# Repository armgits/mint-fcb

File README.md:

# Mint

Mint Flight Controller Board is compact under a 27 mm square to fit on Micro/Nano class drones using a standard 20 x 20 mm mount. Despite the small form factor, it features a comprehensive set of IO interfaces for a wide range of peripherals.

This repository hosts the KiCAD project of the flight controller board.

> - The PCB design is still under completion. This board has never been built and tested.
> - Firmware for this target does not exist yet.

## Specifications

- **Processor and Sensors**
  - STM32H723VIH6 MCU
  - ICM20602 and BMI088 IMUs
  - DPS310 Barometer

- **Interfaces**
  - 10x PWM outputs (8 for motors and 2 for peripherals)
  - 1x RC input (UART 1)
  - 1x I2C bus for external sensors
  - 1x CAN bus for external sensors
  - 5x UARTs
  - 4-in-1 ESC interface for Motor outputs 1-4
  - DJI Air Unit interface (UART 8)
  - 3x GPIO pins
  - 1x microSD card slot for logging

- **Power**
  - 4V - 32V voltage input (2S-7S)
  - Onboard 5V, 2A BEC for low-power peripherals

- **Physical Dimensions**
  - 26.5 x 26.25 mm
  - 20 x 20 mm, M2 mount pattern

## Images

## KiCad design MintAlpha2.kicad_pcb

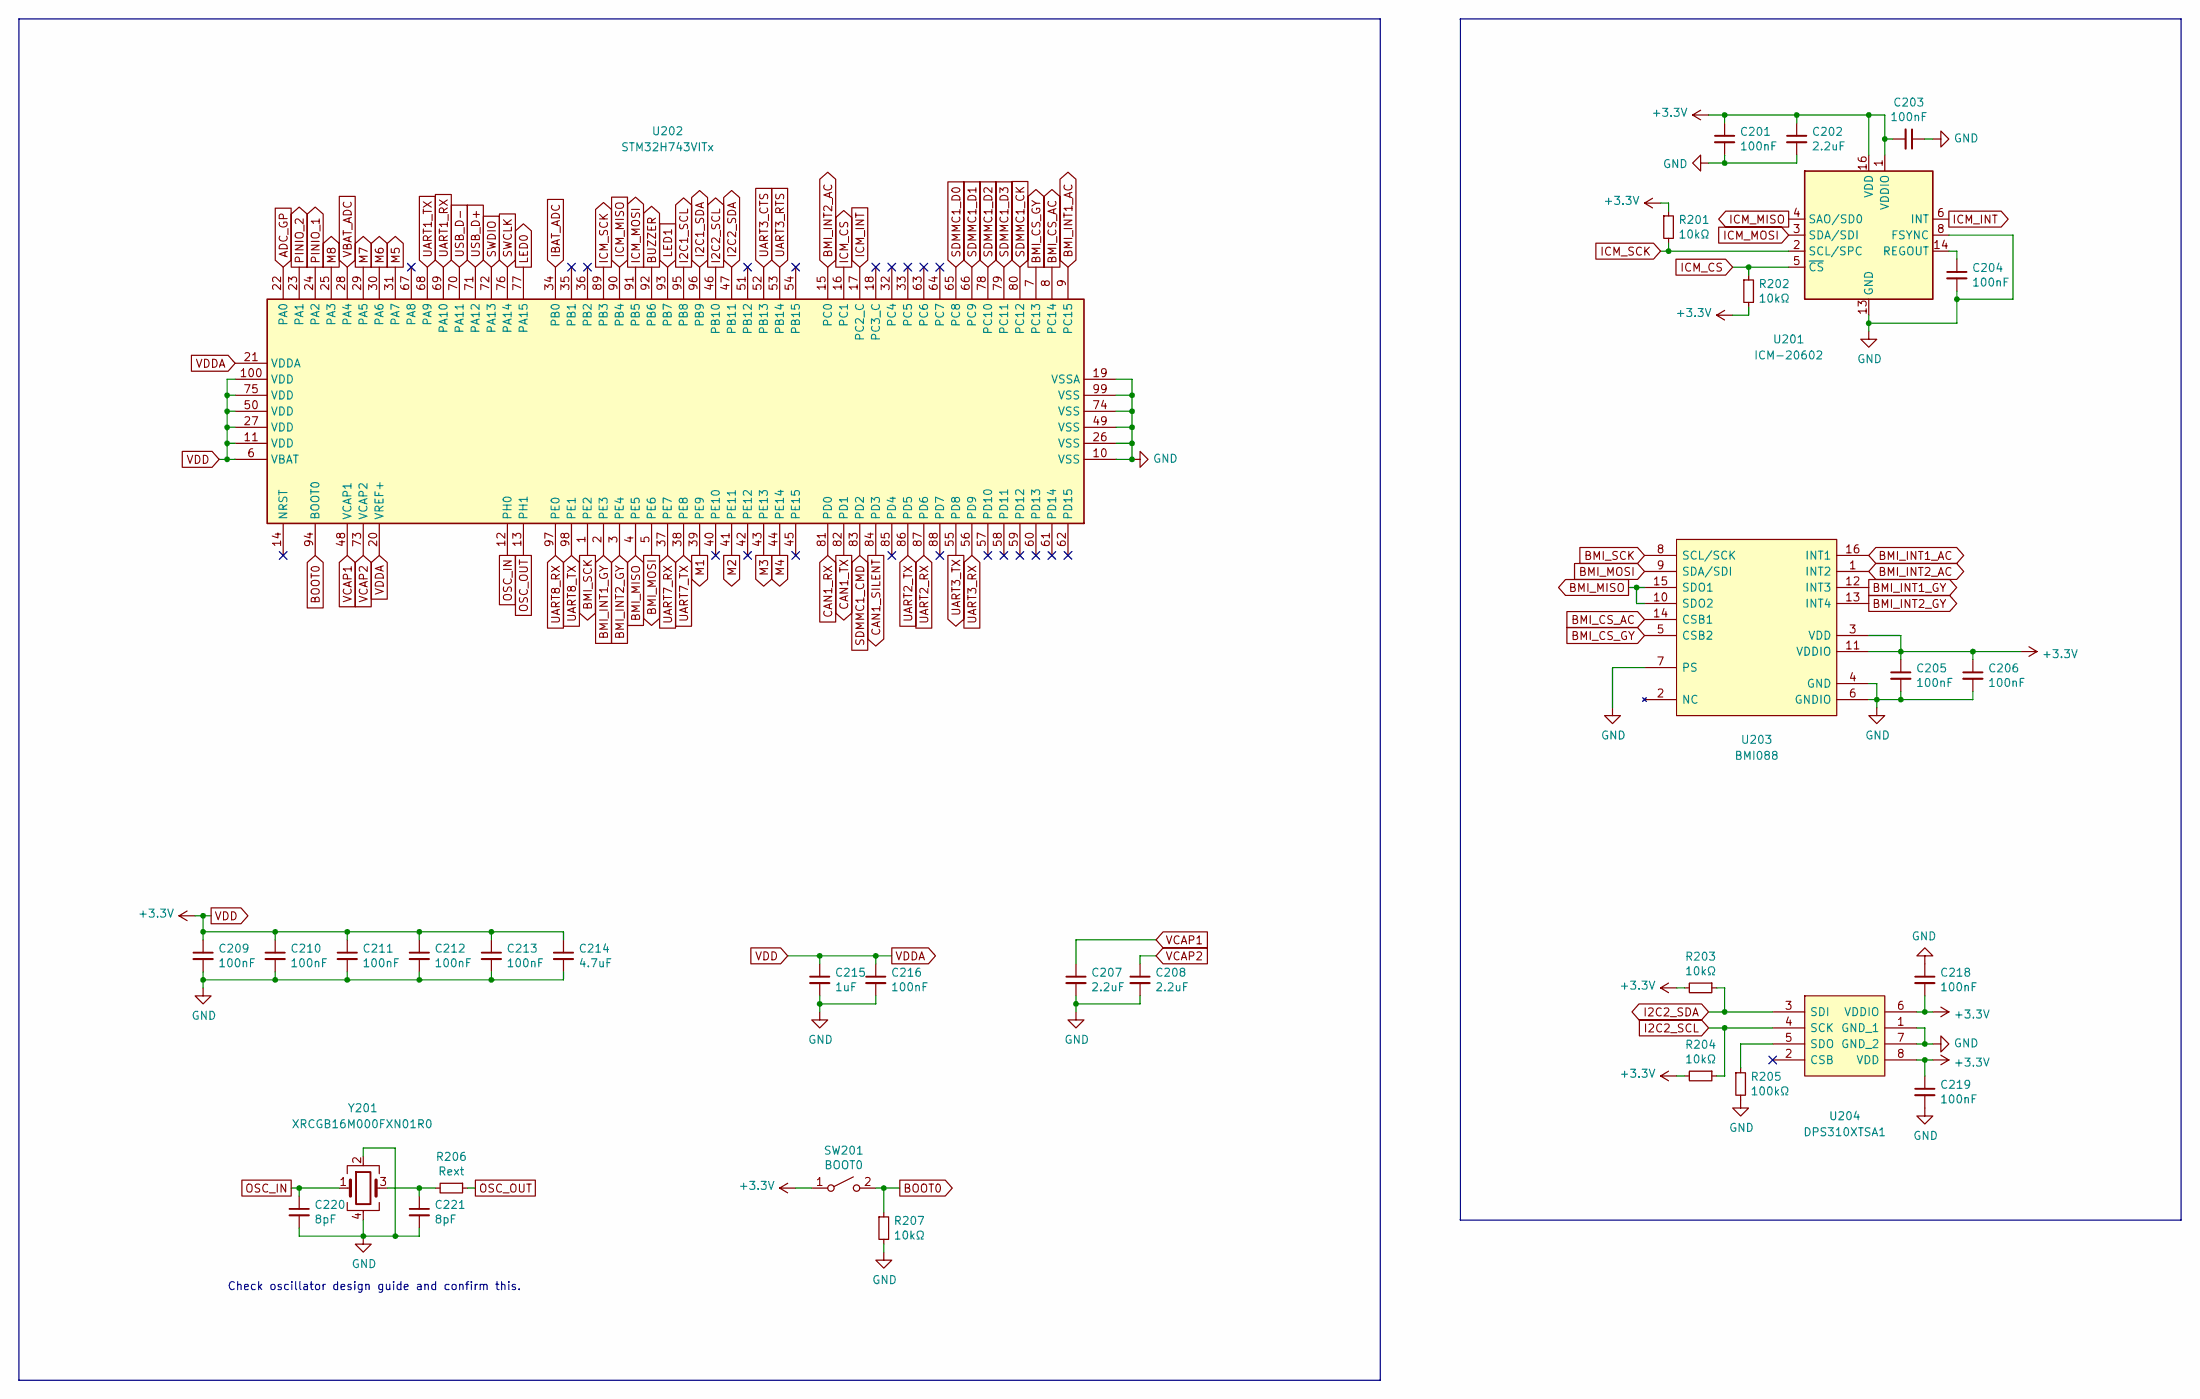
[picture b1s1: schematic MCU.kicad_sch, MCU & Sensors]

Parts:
C201, C203, C204, C205, C206, C209, C210, C211, C212, C213, C216, C218, C219: 100nF; C_0402_1005Metric; Part No. C0402C104K4RAC7411
C202, C207, C208: 2.2uF; C_0402_1005Metric; Part No. LMK105BJ225KV-F
C214: 4.7uF; C_0603_1608Metric; Part No. LMK107BJ475MAHT
C215: 1uF; C_0402_1005Metric; Part No. LMK105BJ105MVHF
C220, C221: 8pF; C_0402_1005Metric; Part No. GJM1555C1H8R0CB01D
R201, R202, R203, R204, R207: 10kΩ; R_0402_1005Metric; Part No. RC0402FR-0710KL
R205: 100kΩ; R_0402_1005Metric; Part No. RC0402FR-07100KL
R206: Rext; R_0402_1005Metric
SW201: BOOT0; TactileSwitch_B3U-1000P_SPST_NO; Part No. KMS233GLFG
U201: ICM-20602; LGA-16_3x3mm_P0.5mm_LayoutBorder3x5y; Part No. ICM-20602
U202: STM32H743VITx; LQFP-100_14x14mm_P0.5mm
U203: BMI088; BMI088_LGA16_4.5x3mm_P0.5mm; Part No. BMI088
U204: DPS310XTSA1; DPS310_PG-VLGA-8-1; Part No. DPS310XTSA1
Y201: XRCGB16M000FXN01R0; Crystal_Murata_XRCGB_F_P_HCR2016; Part No. XRCGB16M000FXN01R0

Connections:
ADC_GP: U202.22 (PA0); also elsewhere on the board
BMI_CS_AC: U202.8 (PC14), U203.14 (CSB1)
BMI_CS_GY: U202.7 (PC13), U203.5 (CSB2)
BMI_INT1_AC: U202.9 (PC15), U203.16 (INT1)
BMI_INT1_GY: U202.2 (PE3), U203.12 (INT3)
BMI_INT2_AC: U202.15 (PC0), U203.1 (INT2)
BMI_INT2_GY: U202.3 (PE4), U203.13 (INT4)
BMI_MISO: U202.4 (PE5), U203.10 (SDO2), U203.15 (SDO1)
BMI_MOSI: U202.5 (PE6), U203.9 (SDA/SDI)
BMI_SCK: U202.1 (PE2), U203.8 (SCL/SCK)
BOOT0: R207.1, SW201.2 (B), U202.94 (BOOT0)
BUZZER: U202.92 (PB6); also elsewhere on the board
CAN1_RX: U202.81 (PD0); also elsewhere on the board
CAN1_SILENT: U202.84 (PD3); also elsewhere on the board
CAN1_TX: U202.82 (PD1); also elsewhere on the board
GND: C201.2, C202.2, C203.1, C204.2, C205.2, C206.2, C207.2, C208.2, C209.2, C210.2, C211.2, C212.2, C213.2, C214.2, C215.2, C216.2, C218.1, C219.2, C220.2, C221.2, R205.2, R207.2, U201.8 (FSYNC), U201.9 (GND), U201.10 (GND), U201.11 (GND), U201.12 (GND), U201.13 (GND), U201.15 (GND), U202.10 (VSS), U202.19 (VSSA), U202.26 (VSS), U202.49 (VSS), U202.74 (VSS), U202.99 (VSS), U203.4 (GND), U203.6 (GNDIO), U203.7 (PS), U204.1 (GND_1), U204.7 (GND_2), Y201.2, Y201.4; also elsewhere on the board
I2C1_SCL: U202.95 (PB8); also elsewhere on the board
I2C1_SDA: U202.96 (PB9); also elsewhere on the board
I2C2_SCL: R204.1, U202.46 (PB10), U204.4 (SCK)
I2C2_SDA: R203.1, U202.47 (PB11), U204.3 (SDI)
IBAT_ADC: U202.34 (PB0); also elsewhere on the board
ICM_CS: R202.1, U201.5 (~CS), U202.16 (PC1)
ICM_INT: U201.6 (INT), U202.17 (PC2_C)
ICM_MISO: U201.4 (SAO/SD0), U202.90 (PB4)
ICM_MOSI: U201.3 (SDA/SDI), U202.91 (PB5)
ICM_SCK: R201.2, U201.2 (SCL/SPC), U202.89 (PB3)
LED0: U202.77 (PA15); also elsewhere on the board
LED1: U202.93 (PB7); also elsewhere on the board
M1: U202.39 (PE9); also elsewhere on the board
M2: U202.41 (PE11); also elsewhere on the board
M3: U202.43 (PE13); also elsewhere on the board
M4: U202.44 (PE14); also elsewhere on the board
M5: U202.31 (PA7); also elsewhere on the board
M6: U202.30 (PA6); also elsewhere on the board
M7: U202.29 (PA5); also elsewhere on the board
M8: U202.25 (PA3); also elsewhere on the board
unnamed: C204.1, U201.14 (REGOUT)
unnamed: C221.1, R206.2, Y201.3
unnamed: R205.1, U204.5 (SDO)
OSC_IN: C220.1, U202.12 (PH0), Y201.1
OSC_OUT: R206.1, U202.13 (PH1)
PINIO_1: U202.24 (PA2); also elsewhere on the board
PINIO_2: U202.23 (PA1); also elsewhere on the board
SDMMC1_CK: U202.80 (PC12); also elsewhere on the board
SDMMC1_CMD: U202.83 (PD2); also elsewhere on the board
SDMMC1_D0: U202.65 (PC8); also elsewhere on the board
SDMMC1_D1: U202.66 (PC9); also elsewhere on the board
SDMMC1_D2: U202.78 (PC10); also elsewhere on the board
SDMMC1_D3: U202.79 (PC11); also elsewhere on the board
SWCLK: U202.76 (PA14); also elsewhere on the board
SWDIO: U202.72 (PA13); also elsewhere on the board
UART1_RX: U202.69 (PA10); also elsewhere on the board
UART1_TX: U202.68 (PA9); also elsewhere on the board
UART2_RX: U202.87 (PD6); also elsewhere on the board
UART2_TX: U202.86 (PD5); also elsewhere on the board
UART3_CTS: U202.52 (PB13); also elsewhere on the board
UART3_RTS: U202.53 (PB14); also elsewhere on the board
UART3_RX: U202.56 (PD9); also elsewhere on the board
UART3_TX: U202.55 (PD8); also elsewhere on the board
UART7_RX: U202.37 (PE7); also elsewhere on the board
UART7_TX: U202.38 (PE8); also elsewhere on the board
UART8_RX: U202.97 (PE0); also elsewhere on the board
UART8_TX: U202.98 (PE1); also elsewhere on the board
USB_D+: U202.71 (PA12); also elsewhere on the board
USB_D-: U202.70 (PA11); also elsewhere on the board
VBAT_ADC: U202.28 (PA4); also elsewhere on the board
VCAP1: C207.1, U202.48 (VCAP1)
VCAP2: C208.1, U202.73 (VCAP2)
VDD: C201.1, C202.1, C203.2, C205.1, C206.1, C209.1, C210.1, C211.1, C212.1, C213.1, C214.1, C215.1, C216.1, C218.2, C219.1, R201.1, R202.2, R203.2, R204.2, SW201.1 (A), U201.1 (VDDIO), U201.16 (VDD), U202.6 (VBAT), U202.11 (VDD), U202.20 (VREF+), U202.21 (VDDA), U202.27 (VDD), U202.50 (VDD), U202.75 (VDD), U202.100 (VDD), U203.3 (VDD), U203.11 (VDDIO), U204.6 (VDDIO), U204.8 (VDD); also elsewhere on the board

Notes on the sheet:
Check oscillator design guide and confirm this.

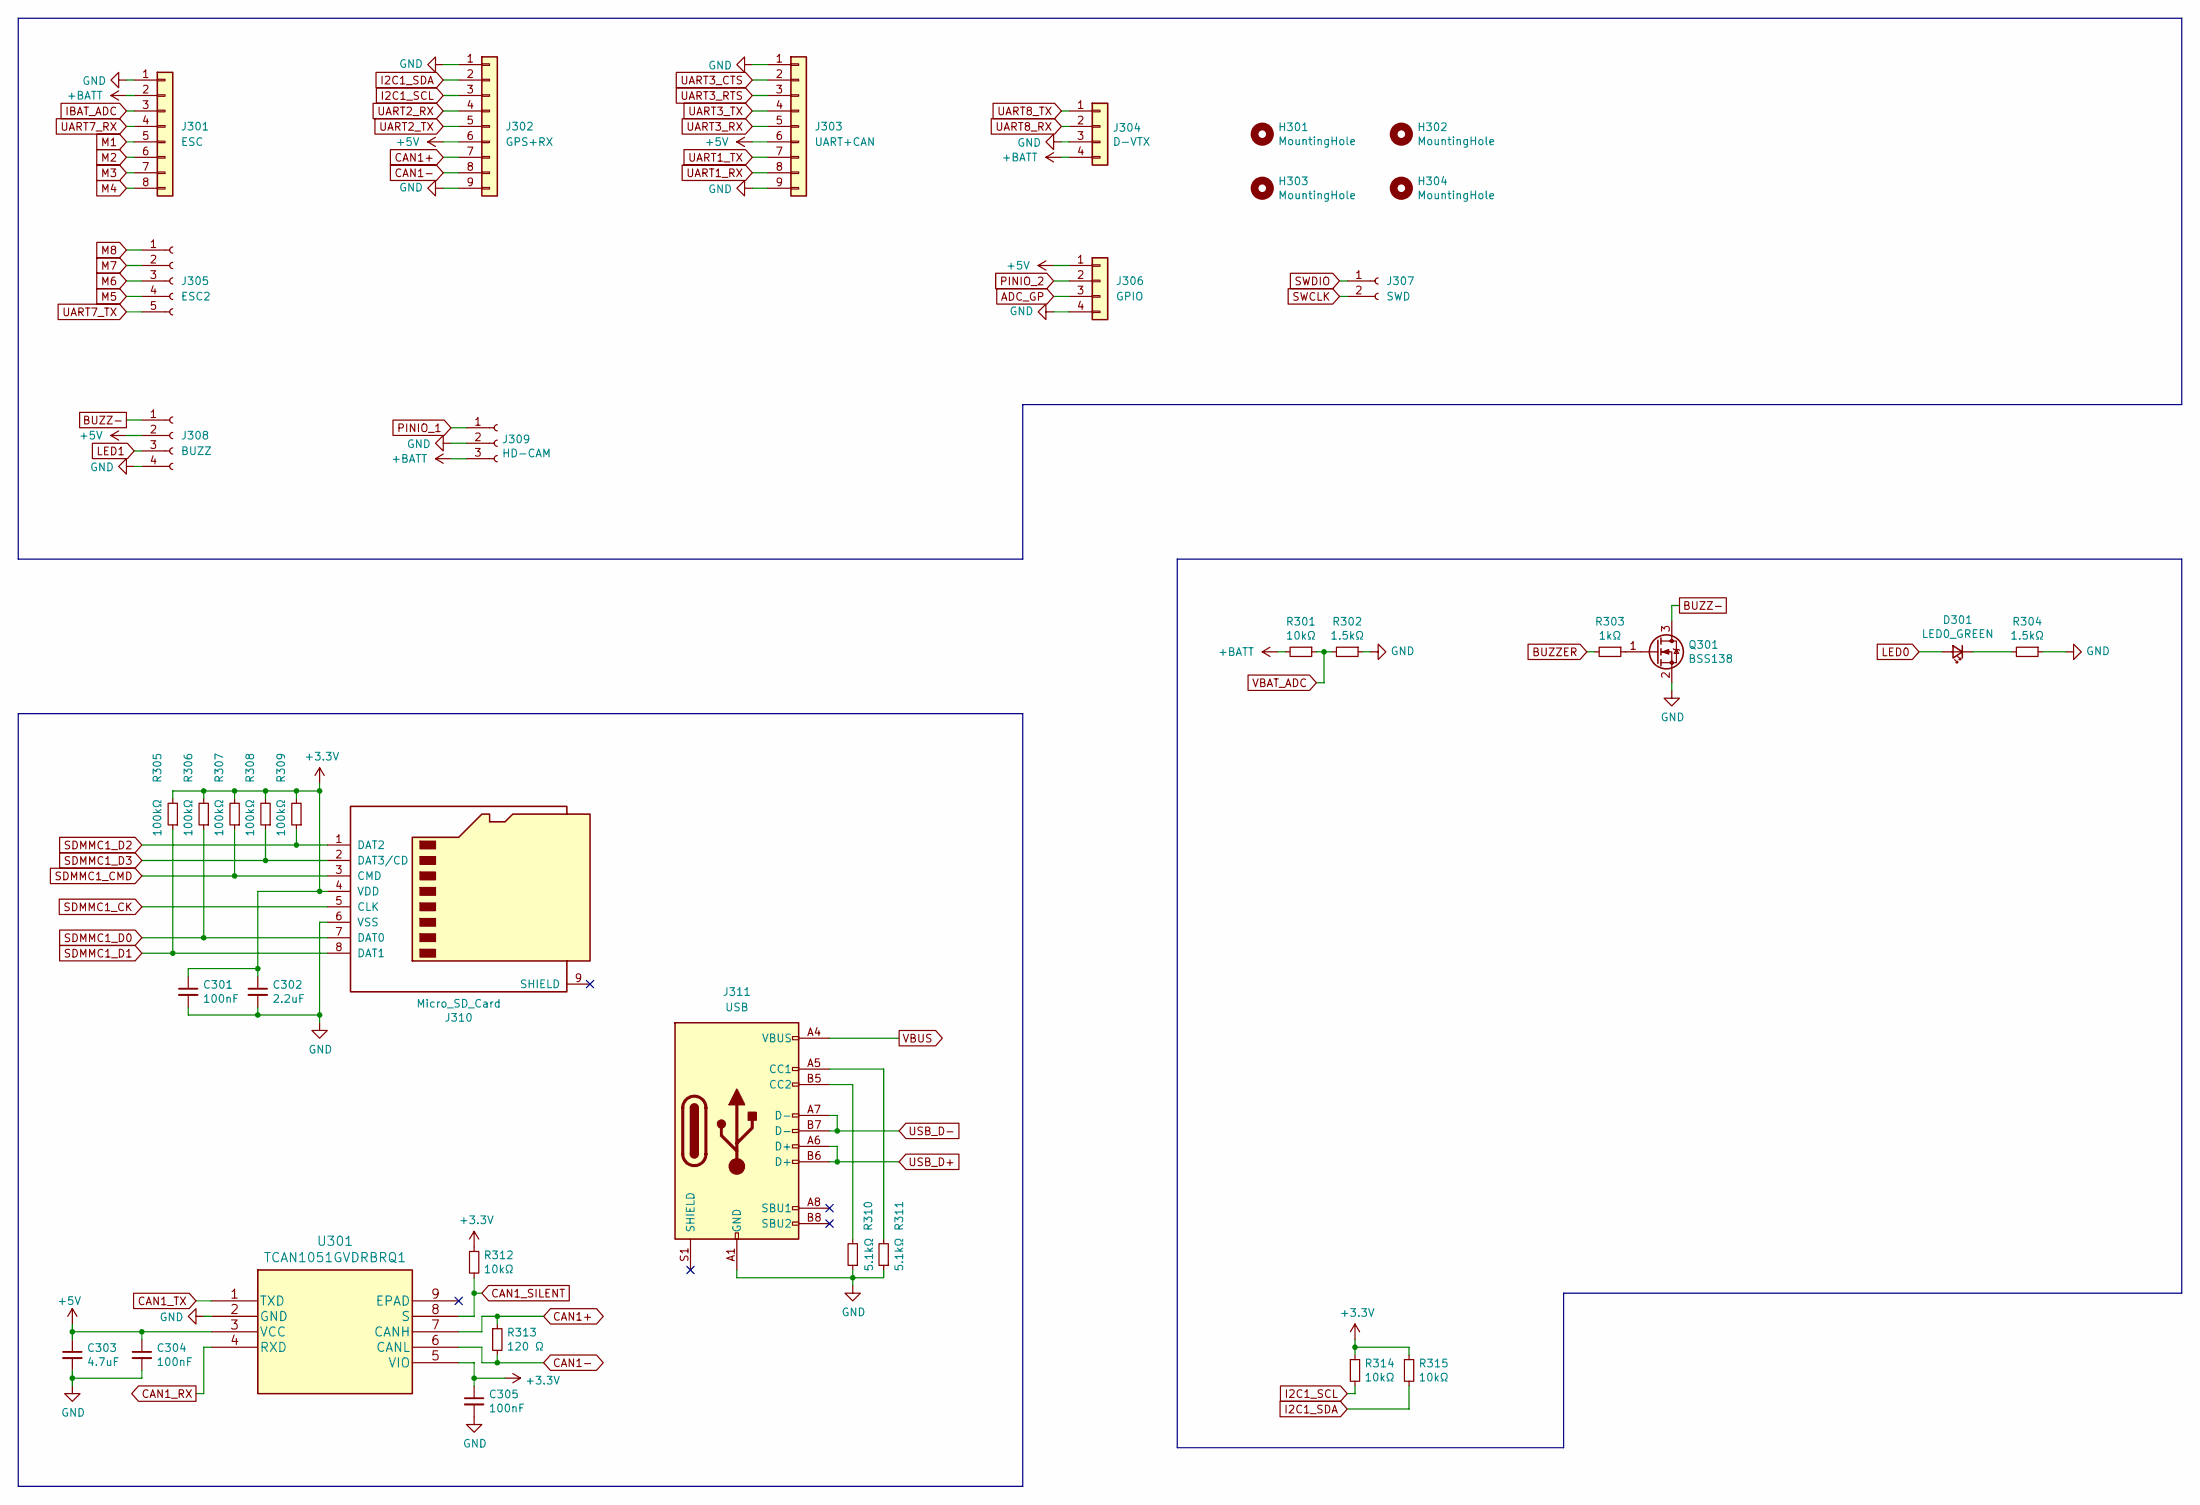
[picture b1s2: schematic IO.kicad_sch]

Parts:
C301, C304, C305: 100nF; C_0402_1005Metric; Part No. C0402C104K4RAC7411
C302: 2.2uF; C_0402_1005Metric; Part No. LMK105BJ225KV-F
C303: 4.7uF; C_0603_1608Metric; Part No. LMK107BJ475MAHT
D301: LED0_GREEN; LED_0603_1608Metric; Part No. KP DELMS1.22-MGNH-25-E6L6
H301, H302, H303, H304: MountingHole; MountingHole_2.2mm_M2_ISO14580
J301: ESC; CustomSolderpads_8x1_2x1mm_P1.75mm; Part No. SM08B-SRSS-TB(LF)(SN)
J302: GPS+RX; SideSolderpads_9x1_2x1mm_P1.75mm
J303: UART+CAN; SideSolderpads_9x1_2x1mm_P1.75mm
J304: D-VTX; CustomSolderpads_4x1_2x1mm_P1.75mm; Part No. SM06B-SRSS-TB(LF)(SN)
J305: ESC2; Solderpads_5x1_2x1mm_P1.75mm
J306: GPIO; Solderpads_4x1_2x1mm_P1.75mm
J307: SWD; CustomPinHeader_1x02_P2.00mm_Vertical
J308: BUZZ; SideSolderpads_4x1_2x1mm_P1.75mm
J309: HD-CAM; CustomSolderpads_3x1_2x1mm_P1.75mm
J310: Micro_SD_Card; MicroSD_Molex_475710001; Part No. 47571-0001
J311: USB; USB-C_GF-USB4110; Part No. USB4110-GF-A
Q301: BSS138; SOT-23
R301, R312, R314, R315: 10kΩ; R_0402_1005Metric; Part No. RC0402FR-0710KL
R302, R304: 1.5kΩ; R_0402_1005Metric; Part No. RC0402FR-071K5L
R303: 1kΩ; R_0402_1005Metric; Part No. RC0402FR-071KL
R305, R306, R307, R308, R309: 100kΩ; R_0402_1005Metric; Part No. RC0402FR-07100KL
R310, R311: 5.1kΩ; R_0402_1005Metric; Part No. RC0402FR-075K1L
R313: 120 Ω; R_0402_1005Metric; Part No. CRCW0603120RFKEAC
U301: TCAN1051GVDRBRQ1; Part No. TCAN1051GVDRBRQ1

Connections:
+5V: C303.1, C304.1, J302.6, J303.6, J306.1, J308.2, U301.3 (VCC); also elsewhere on the board
+BATT: J301.2, J304.4, J309.3, R301.2; also elsewhere on the board
ADC_GP: J306.3; also elsewhere on the board
BUZZ-: J308.1, Q301.3 (D)
BUZZER: R303.2; also elsewhere on the board
CAN1+: J302.7, R313.1, U301.7 (CANH)
CAN1-: J302.8, R313.2, U301.6 (CANL)
CAN1_RX: U301.4 (RXD); also elsewhere on the board
CAN1_SILENT: R312.2, U301.8 (S); also elsewhere on the board
CAN1_TX: U301.1 (TXD); also elsewhere on the board
GND: C301.2, C302.2, C303.2, C304.2, C305.2, J301.1, J302.1, J302.9, J303.1, J303.9, J304.3, J306.4, J308.4, J309.2, J310.6 (VSS), J311.A1 (GND), J311.A12 (GND), J311.B1 (GND), J311.B12 (GND), Q301.2 (S), R302.1, R304.1, R310.1, R311.1, U301.2 (GND); also elsewhere on the board
I2C1_SCL: J302.3, R314.2; also elsewhere on the board
I2C1_SDA: J302.2, R315.2; also elsewhere on the board
IBAT_ADC: J301.3; also elsewhere on the board
LED0: D301.2 (A); also elsewhere on the board
LED1: J308.3; also elsewhere on the board
M1: J301.5; also elsewhere on the board
M2: J301.6; also elsewhere on the board
M3: J301.7; also elsewhere on the board
M4: J301.8; also elsewhere on the board
M5: J305.4; also elsewhere on the board
M6: J305.3; also elsewhere on the board
M7: J305.2; also elsewhere on the board
M8: J305.1; also elsewhere on the board
unnamed: D301.1 (K), R304.2
unnamed: J311.A5 (CC1), R311.2
unnamed: J311.B5 (CC2), R310.2
unnamed: Q301.1 (G), R303.1
PINIO_1: J309.1; also elsewhere on the board
PINIO_2: J306.2; also elsewhere on the board
SDMMC1_CK: J310.5 (CLK); also elsewhere on the board
SDMMC1_CMD: J310.3 (CMD), R307.1; also elsewhere on the board
SDMMC1_D0: J310.7 (DAT0), R306.1; also elsewhere on the board
SDMMC1_D1: J310.8 (DAT1), R305.1; also elsewhere on the board
SDMMC1_D2: J310.1 (DAT2), R309.1; also elsewhere on the board
SDMMC1_D3: J310.2 (DAT3/CD), R308.1; also elsewhere on the board
SWCLK: J307.2; also elsewhere on the board
SWDIO: J307.1; also elsewhere on the board
UART1_RX: J303.8; also elsewhere on the board
UART1_TX: J303.7; also elsewhere on the board
UART2_RX: J302.4; also elsewhere on the board
UART2_TX: J302.5; also elsewhere on the board
UART3_CTS: J303.2; also elsewhere on the board
UART3_RTS: J303.3; also elsewhere on the board
UART3_RX: J303.5; also elsewhere on the board
UART3_TX: J303.4; also elsewhere on the board
UART7_RX: J301.4; also elsewhere on the board
UART7_TX: J305.5; also elsewhere on the board
UART8_RX: J304.2; also elsewhere on the board
UART8_TX: J304.1; also elsewhere on the board
USB_D+: J311.A6 (D+), J311.B6 (D+); also elsewhere on the board
USB_D-: J311.A7 (D-), J311.B7 (D-); also elsewhere on the board
VBAT_ADC: R301.1, R302.2; also elsewhere on the board
VBUS: J311.A4 (VBUS), J311.A9 (VBUS), J311.B4 (VBUS), J311.B9 (VBUS); also elsewhere on the board
VDD: C301.1, C302.1, C305.1, J310.4 (VDD), R305.2, R306.2, R307.2, R308.2, R309.2, R312.1, R314.1, R315.1, U301.5 (VIO); also elsewhere on the board

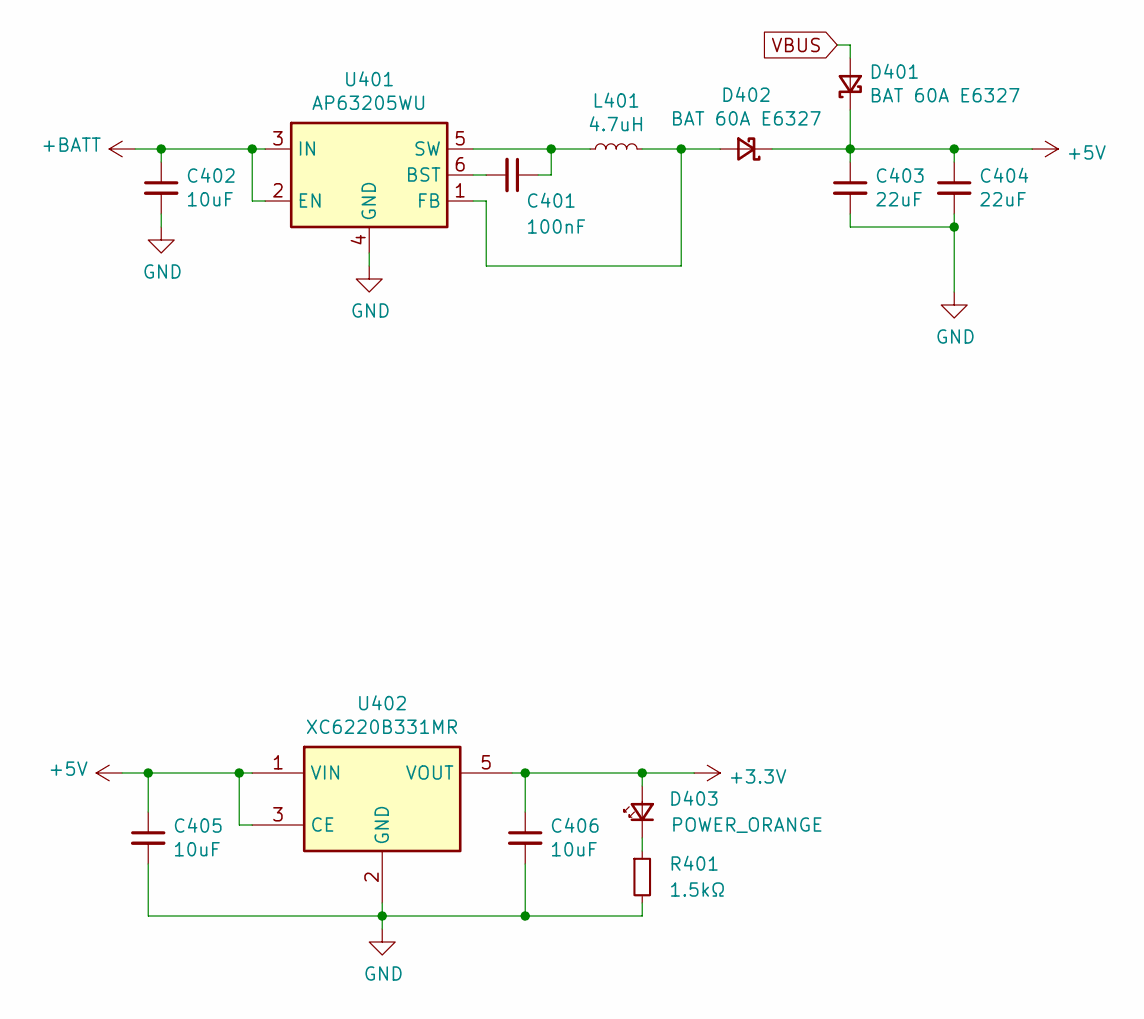
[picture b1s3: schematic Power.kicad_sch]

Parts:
C401: 100nF; C_0402_1005Metric; Part No. C0402C104K4RAC7411
C402: 10uF; C_1206_3216Metric; Part No. UMK316BBJ106KL-T
C403, C404: 22uF; C_0805_2012Metric; Part No. GRM21BR61A226ME51L
C405, C406: 10uF; C_0805_2012Metric; Part No. GRM21BR61C106KE15K
D401, D402: BAT 60A E6327; D_SOD-323; Part No. BAT 60A E6327
D403: POWER_ORANGE; LED_0603_1608Metric; Part No. KO DELLS1.22-KHLI-24
L401: 4.7uH; L_Taiyo-Yuden_NR-50xx; Part No. NRS5030T4R7MMGJ
R401: 1.5kΩ; R_0402_1005Metric; Part No. RC0402FR-071K5L
U401: AP63205WU; TSOT-23-6
U402: XC6220B331MR; SOT-23-5

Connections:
+5V: C403.1, C404.1, C405.1, D401.1 (K), D402.1 (K), U402.1 (VIN), U402.3 (CE); also elsewhere on the board
+BATT: C402.1, U401.2 (EN), U401.3 (IN); also elsewhere on the board
GND: C402.2, C403.2, C404.2, C405.2, C406.2, R401.2, U401.4 (GND), U402.2 (GND); also elsewhere on the board
unnamed: C401.1, L401.1, U401.5 (SW)
unnamed: C401.2, U401.6 (BST)
unnamed: D402.2 (A), L401.2, U401.1 (FB)
unnamed: D403.1 (K), R401.1
VBUS: D401.2 (A); also elsewhere on the board
VDD: C406.1, D403.2 (A), U402.5 (VOUT); also elsewhere on the board

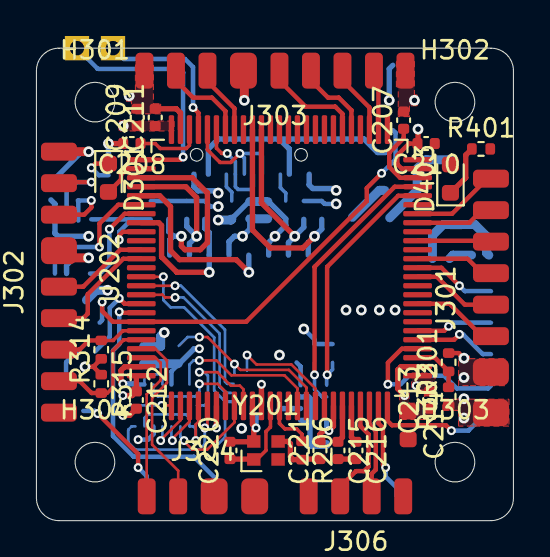
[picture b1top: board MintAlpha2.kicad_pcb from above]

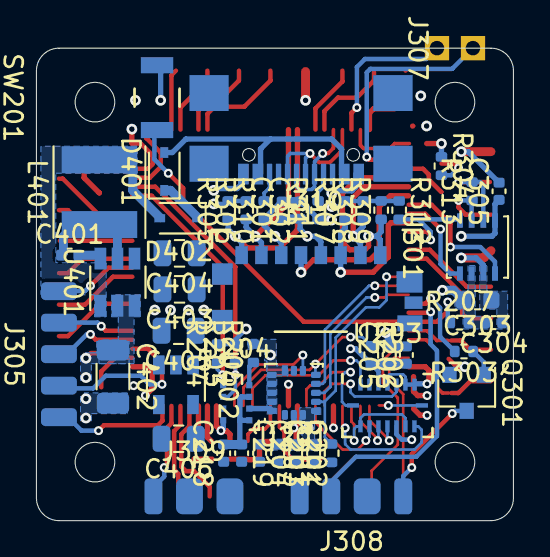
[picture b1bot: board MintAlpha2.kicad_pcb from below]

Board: 4 copper layers, 26.5 x 26.2 mm, 84 parts (53 on the bottom side), 83 nets.

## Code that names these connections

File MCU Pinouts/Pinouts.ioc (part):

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PB10.Mode=I2C
PC12.Signal=SDMMC1_CK
PA15\ (JTDI).Signal=GPIO_Output
PB13.Signal=USART3_CTS
PA14\ (JTCK/SWCLK).Signal=DEBUG_JTCK-SWCLK
PE2.Mode=Full_Duplex_Master
PB6.Signal=TIM16_CH1N
PB6.Mode=PWM Generation1 CH1N
PD0.Signal=FDCAN1_RX
PD8.Signal=USART3_TX
PE5.Signal=SPI4_MISO
PE1.Signal=UART8_TX
PE9.Signal=S_TIM1_CH1
PB14.Mode=CTS_RTS
PA0.Mode=IN16-Single-Ended
PC9.Mode=SD_4_bits_Wide_bus
PE2.Signal=SPI4_SCK
PA14\ (JTCK/SWCLK).Mode=Serial_Wire
PA0.Signal=ADC1_INP16
Mcu.Package=LQFP100
PB9.Signal=I2C1_SDA
PA10.Signal=USART1_RX
PC11.Mode=SD_4_bits_Wide_bus
PB13.Mode=CTS_RTS
PH0-OSC_IN\ (PH0).Mode=HSE-External-Oscillator
PC13.Signal=EVENTOUT
PD3.Signal=GPIO_Output
PE1.Mode=Asynchronous
PD7.Signal=GPIO_Output
PD1.Signal=FDCAN1_TX
PC0.Signal=EVENTOUT
PD6.Mode=Asynchronous
PE8.Mode=Asynchronous
PB11.Mode=I2C
PA9.Signal=USART1_TX
PD8.Mode=Asynchronous
PB10.Signal=I2C2_SCL
PB14.Signal=USART3_RTS
PA5.Signal=S_TIM2_CH1
PC12.Mode=SD_4_bits_Wide_bus
PD1.Mode=FDCANFD
PE14.Signal=S_TIM1_CH4
PE6.Mode=Full_Duplex_Master
PE15.Signal=GPIO_Output
PE8.Signal=UART7_TX
PB4\ (NJTRST).Mode=Full_Duplex_Master
PC8.Mode=SD_4_bits_Wide_bus
PA4.Signal=ADCx_INP18
PB5.Signal=SPI1_MOSI
PA11.Signal=USB_OTG_FS_DM
PB3\ (JTDO/TRACESWO).Mode=Full_Duplex_Master
PB8.Mode=I2C
PE3.Signal=GPIO_Output
PD2.Signal=SDMMC1_CMD
PB0.Signal=ADCx_INP9
PC1.Signal=GPIO_Output
PA13\ (JTMS/SWDIO).Signal=DEBUG_JTMS-SWDIO
Mcu.UserName=STM32H743VITx
PH0-OSC_IN\ (PH0).Signal=RCC_OSC_IN
PC10.Signal=SDMMC1_D2
PA11.Mode=Device_Only
PB11.Signal=I2C2_SDA
PD9.Mode=Asynchronous
PA12.Signal=USB_OTG_FS_DP
PC2_C.Signal=EVENTOUT
PD5.Mode=Asynchronous
PH1-OSC_OUT\ (PH1).Mode=HSE-External-Oscillator
PE13.Signal=S_TIM1_CH3
PB5.Mode=Full_Duplex_Master
PB7.Signal=S_TIM4_CH2
PE4.Signal=GPIO_Output
PA6.Signal=S_TIM3_CH1
PE7.Signal=UART7_RX
PD6.Signal=USART2_RX
PA3.Signal=S_TIM2_CH4
PA13\ (JTMS/SWDIO).Mode=Serial_Wire
PA10.Mode=Asynchronous
PC11.Signal=SDMMC1_D3
PC8.Signal=SDMMC1_D0
PC10.Mode=SD_4_bits_Wide_bus
PD5.Signal=USART2_TX
PD9.Signal=USART3_RX
PH1-OSC_OUT\ (PH1).Signal=RCC_OSC_OUT
PA9.Mode=Asynchronous
PB3\ (JTDO/TRACESWO).Signal=SPI1_SCK
PC15-OSC32_OUT\ (OSC32_OUT).Signal=EVENTOUT
PB9.Mode=I2C
PE11.Signal=S_TIM1_CH2
PA1.Signal=GPIO_Output
PD2.Mode=SD_4_bits_Wide_bus
board=custom
PE5.Mode=Full_Duplex_Master
PE6.Signal=SPI4_MOSI
PE0.Signal=UART8_RX
Mcu.Name=STM32H743VITx
PD0.Mode=FDCANFD
PA2.Signal=GPIO_Output
RCC.SYSCLKFreq_VALUE=64000000
PE7.Mode=Asynchronous
PA12.Mode=Device_Only
PC14-OSC32_IN\ (OSC32_IN).Signal=EVENTOUT
PB8.Signal=I2C1_SCL
PC9.Signal=SDMMC1_D1
PE0.Mode=Asynchronous
PA7.Signal=S_TIM3_CH2
PB4\ (NJTRST).Signal=SPI1_MISO

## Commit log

2024-02-28 Fixed MCU pinout description
2024-02-28 Cropped images to square
2024-02-28 Add README
2024-02-28 Removed image captions
2024-02-28 Removed brackets around voltage range
2024-02-28 Added hole size in mount description
2024-02-28 Fixed a typo in Footprints library name
2024-02-28 Added microSD card slot to interfaces list
2024-03-23 Create LICENSE
